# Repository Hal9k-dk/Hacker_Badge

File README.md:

# Hacker_Badge
HAL9K member PCB badge 
See more at http://wiki.hal9k.dk/projects/hacker_badge

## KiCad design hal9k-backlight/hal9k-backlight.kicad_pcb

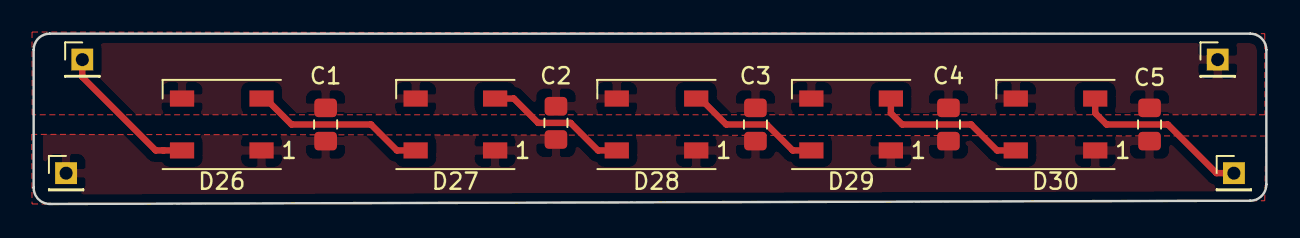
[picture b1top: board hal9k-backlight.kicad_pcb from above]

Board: 2 copper layers, 76.0 x 10.5 mm, 14 parts (0 on the bottom side), 8 nets.

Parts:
C1, C2, C3, C4, C5: C; C_0805_2012Metric_Pad1.15x1.40mm_HandSolder
D26, D27, D28, D29, D30: WS2812B; LED_WS2812B_PLCC4_5.0x5.0mm_P3.2mm
J1: +; PinHeader_1x01_P2.00mm_Vertical
J2: GND; PinHeader_1x01_P2.00mm_Vertical
J3: Din; PinHeader_1x01_P2.00mm_Vertical
J4: Dout; PinHeader_1x01_P2.00mm_Vertical

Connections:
+BATT: C1.1, C2.1, C3.1, C4.1, C5.1, D26.1, D27.1, D28.1, D29.1, D30.1, J1.1
GND: C1.2, C2.2, C3.2, C4.2, C5.2, D26.3, D27.3, D28.3, D29.3, D30.3, J2.1
unnamed: D26.2, D27.4
unnamed: D26.4, J3.1
unnamed: D27.2, D28.4
unnamed: D28.2, D29.4
unnamed: D29.2, D30.4
unnamed: D30.2, J4.1

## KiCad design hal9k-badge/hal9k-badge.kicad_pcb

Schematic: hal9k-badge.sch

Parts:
C1, C6: 10uF; C_0805_HandSoldering
C2, C5, C7, C8, C9, C10, C11, C12, C13, C14, C15, C16, C17, C18, C19, C20, C21, C22, C23, C24, C25, C26, C27, C28, C29, C30, C31, C32, C33, C34, C35, C36: 100nF; C_0805_HandSoldering
C3, C4: 1uF; C_0805_HandSoldering
C37, C38, C39, C40: 22pF; C_0603_HandSoldering
D1, D2, D3, D4, D5, D6, D7, D8, D9, D10, D11, D12, D13, D14, D15, D16, D17, D18, D19, D20, D21, D22, D23, D24, D25: WS2812B; LED_WS2812B_PLCC4_5.0x5.0mm_P3.2mm
D26: 1N5819; D_0805_2012Metric_Pad1.15x1.40mm_HandSolder
D27: L13; LED_0603_1608Metric_Pad1.05x0.95mm_HandSolder
D28: USB; LED_0603_1608Metric_Pad1.05x0.95mm_HandSolder
J1: Din; PinHeader_1x01_P2.00mm_Vertical
J2: +; PinHeader_1x01_P2.00mm_Vertical
J3, J13, J14: GND; PinHeader_1x01_P2.00mm_Vertical
J4: Dout; PinHeader_1x01_P2.00mm_Vertical
J5: USB_B_Micro; USB_Micro-B_Molex_47346-0001
J6: ISCP_ATMEGA; Pin_Header_Straight_2x03_Pitch2.54mm
J7: SHITTY_ADD_ON; Pin_Header_Straight_2x02_Pitch2.54mm
J8: Display; Pin_Header_Straight_1x04_Pitch2.54mm
J15: IO_ATMEGA; PinHeader_1x20_P2.00mm_Vertical
J16: IO_ESP; PinHeader_1x12_P2.00mm_Vertical
JP1: DTR_ESP; SolderJumper-2_P1.3mm_Bridged_Pad1.0x1.5mm
JP2: RTS_ESP; SolderJumper-2_P1.3mm_Bridged_Pad1.0x1.5mm
JP3: DTR_ATMEGA; SolderJumper-2_P1.3mm_Bridged_Pad1.0x1.5mm
JP4: SolderJumper_2_Bridged; SolderJumper-2_P1.3mm_Bridged_Pad1.0x1.5mm
JP5: SDA; SolderJumper-3_P1.3mm_Open_Pad1.0x1.5mm_NumberLabels
JP6: WS2812B; SolderJumper-3_P1.3mm_Open_Pad1.0x1.5mm_NumberLabels
JP7: SCL; SolderJumper-3_P1.3mm_Open_Pad1.0x1.5mm_NumberLabels
JP8: TX-RX; SolderJumper-2_P1.3mm_Open_Pad1.0x1.5mm
JP9: RX-TX; SolderJumper-2_P1.3mm_Open_Pad1.0x1.5mm
M1: lipo-charger
Q1, Q2: S8050; SOT-23
R1, R2, R3, R4, R5, R6, R9, R10, R13, R14: 10kOHM; R_0805_HandSoldering
R7, R8: 47OHM; R_0805_HandSoldering
R11, R12: 330OHM; R_0805_HandSoldering
S1: Reset Esp; SW_SPST_FSMSM
S2: SELECT; SW_SPDT_PCM12
S3: Reset Atmega; SW_SPST_FSMSM
S4: POWER; SW_SPDT_PCM12
U1: ESP-12F; ESP-12_SMD
U2: PMIC-LDO-XC6206P332MR-G(SOT23); SOT-23
U3: CH340G; SOIC-16_3.9x9.9mm_Pitch1.27mm
U4: ATmega328P-AU; TQFP-32_7x7mm_P0.8mm
U5: MC14053BDG; SOIC-16_3.9x9.9mm_Pitch1.27mm
Y1: 12MHz; OSC_CSTCE16M0V53-R0
Y2: 16MHz; OSC_CSTCE16M0V53-R0
Y3: 12MHz; Crystal_SMD_HC49-SD
Y4: 16MHz; Crystal_SMD_HC49-SD

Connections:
+3V3: C4.1, C6.1, C8.1, C11.1, S2.1, U2.2, U3.4, U3.16, U5.16
+5V: C3.1, D26.1 (K), R12.2, U2.3
+BATT: C1.1, C2.1, C7.1, C12.1, C13.1, C14.1, C15.1, C16.1, C17.1, C18.1, C19.1, C20.1, C21.1, C22.1, C23.1, C24.1, C25.1, C26.1, C27.1, C28.1, C29.1, C30.1, C31.1, C32.1, C33.1, C34.1, C35.1, C36.1, D1.1, D2.1, D3.1, D4.1, D5.1, D6.1, D7.1, D8.1, D9.1, D10.1, D11.1, D12.1, D13.1, D14.1, D15.1, D16.1, D17.1, D18.1, D19.1, D20.1, D21.1, D22.1, D23.1, D24.1, D25.1, J2.1, J7.2, J8.2, J15.19, J16.1, R1.1, R2.1, R3.1, R9.2, R10.2, R13.2, R14.2, S4.2, U1.8, U4.4 (VCC), U4.6 (VCC), U4.18 (AVCC)
ATMEGA_2: J15.1, U4.32 (PD2)
ATMEGA_3: J15.2, U4.1 (PD3)
ATMEGA_4: J15.3, U4.2 (PD4)
ATMEGA_5: J15.4, U4.9 (PD5)
ATMEGA_6: J15.5, JP6.1, U4.10 (PD6)
ATMEGA_7: J15.6, U4.11 (PD7)
ATMEGA_8: J15.7, U4.12 (PB0)
ATMEGA_9: J15.8, U4.13 (PB1)
ATMEGA_10: J15.9, U4.14 (PB2)
ATMEGA_11: J6.4, J15.10, U4.15 (PB3)
ATMEGA_12: J6.1, J15.11, U4.16 (PB4)
ATMEGA_13: J6.3, J15.12, R11.2, U4.17 (PB5)
ATMEGA_A0: J15.13, U4.23 (PC0)
ATMEGA_A1: J15.14, U4.24 (PC1)
ATMEGA_A2: J15.15, U4.25 (PC2)
ATMEGA_A3: J15.16, U4.26 (PC3)
ATMEGA_A4_SDA: J15.17, JP5.1, U4.27 (PC4)
ATMEGA_A5_SCL: J15.18, JP7.1, U4.28 (PC5)
ATMEGA_A6: U4.19 (ADC6)
ATMEGA_A7: U4.22 (ADC7)
ATMEGA_AREF: C9.1, U4.20 (AREF)
ATMEGA_RESET: C10.1, J6.5, R10.1, S3.2, U4.29 (~RESET~/PC6)
ATMEGA_RX: JP9.2, U4.30 (PD0), U5.12
ATMEGA_TX: JP8.2, U4.31 (PD1), U5.2
CH340_ATMEGA_DTR: JP3.1, U5.5
CH340_DTR: U3.13, U5.4
CH340_ESP_DTR: JP1.1, U5.3
CH340_RTS: JP2.1, U3.14
CH340_RX: R8.1, U5.15
CH340_TX: R7.1, U5.14
ESP_0: J16.6, Q2.3, R2.2, U1.12
ESP_2: J16.5, R3.2, U1.11
ESP_4_SDA: J16.7, JP5.3, U1.13
ESP_5_SCL: J16.8, JP7.3, U1.14
ESP_12: J16.3, U1.6
ESP_13: J16.2, U1.7
ESP_14: J16.10, U1.5
ESP_15: J16.4, R4.2, U1.10
ESP_16: J16.11, U1.4
ESP_ADC: J16.12, U1.2
ESP_CHPD: R1.2, U1.3
ESP_RESET: C5.2, Q1.3, R9.1, S1.2, U1.1
ESP_RX: JP6.3, JP8.1, U1.15, U5.13
ESP_TX: JP9.1, U1.16, U5.1
FTDI_ATMEGA_DTR: C10.2, JP3.2
FTDI_ESP_DTR: JP1.2, Q2.2, R5.1
FTDI_ESP_RTS: JP2.2, Q1.2, R6.1
GND: C1.2, C2.2, C3.2, C4.2, C5.1, C6.2, C7.2, C8.2, C9.2, C11.2, C12.2, C13.2, C14.2, C15.2, C16.2, C17.2, C18.2, C19.2, C20.2, C21.2, C22.2, C23.2, C24.2, C25.2, C26.2, C27.2, C28.2, C29.2, C30.2, C31.2, C32.2, C33.2, C34.2, C35.2, C36.2, C37.2, C38.2, C39.1, C40.1, D1.3, D2.3, D3.3, D4.3, D5.3, D6.3, D7.3, D8.3, D9.3, D10.3, D11.3, D12.3, D13.3, D14.3, D15.3, D16.3, D17.3, D18.3, D19.3, D20.3, D21.3, D22.3, D23.3, D24.3, D25.3, D27.1, D28.1, J3.1, J5.5, J5.6, J6.6, J7.1, J8.1, J13.1, J14.1, J15.20, J16.9, JP4.1, M1.2, M1.3, R4.1, S1.1, S2.3, S3.1, U1.9, U2.1, U3.1, U4.3 (GND), U4.5 (GND), U4.21 (GND), U5.7, U5.8, Y1.2, Y2.2
I2C_SCL: J7.3, J8.3, JP7.2, R13.1
I2C_SDA: J7.4, J8.4, JP5.2, R14.1
unnamed: C37.1, U3.7, Y1.1, Y3.2
unnamed: C38.1, U3.8, Y1.3, Y3.1
unnamed: C39.2, U4.7 (XTAL1/PB6), Y2.3, Y4.1
unnamed: C40.2, U4.8 (XTAL2/PB7), Y2.1, Y4.2
unnamed: D1.2, D2.4
unnamed: D2.2, D3.4
unnamed: D3.2, D4.4
unnamed: D4.2, D5.4
unnamed: D5.2, D6.4
unnamed: D6.2, D7.4
unnamed: D7.2, D8.4
unnamed: D8.2, D9.4
unnamed: D10.2, D11.4
unnamed: D9.2, D10.4
unnamed: D11.2, D12.4
unnamed: D12.2, D13.4
unnamed: D13.2, D14.4
unnamed: D14.2, D15.4
unnamed: D15.2, D16.4
unnamed: D16.2, D17.4
unnamed: D17.2, D18.4
unnamed: D18.2, D19.4
unnamed: D19.2, D20.4
unnamed: D20.2, D21.4
unnamed: D21.2, D22.4
unnamed: D22.2, D23.4
unnamed: D23.2, D24.4
unnamed: D24.2, D25.4
unnamed: D25.2, J1.1
unnamed: D27.2, R11.1
unnamed: D28.2, R12.1
unnamed: J5.2, U3.6
unnamed: J5.3, U3.5
unnamed: JP4.2, U5.6
unnamed: M1.6, S4.3
unnamed: Q1.1, R5.2
unnamed: Q2.1, R6.2
unnamed: R7.2, U3.2
unnamed: R8.2, U3.3
unnamed: S2.2, U5.9, U5.10, U5.11
VCC: D26.2 (A), J5.1, M1.1
WS2812B_Din: D1.4, JP6.2
WS2812B_Dout: J4.1

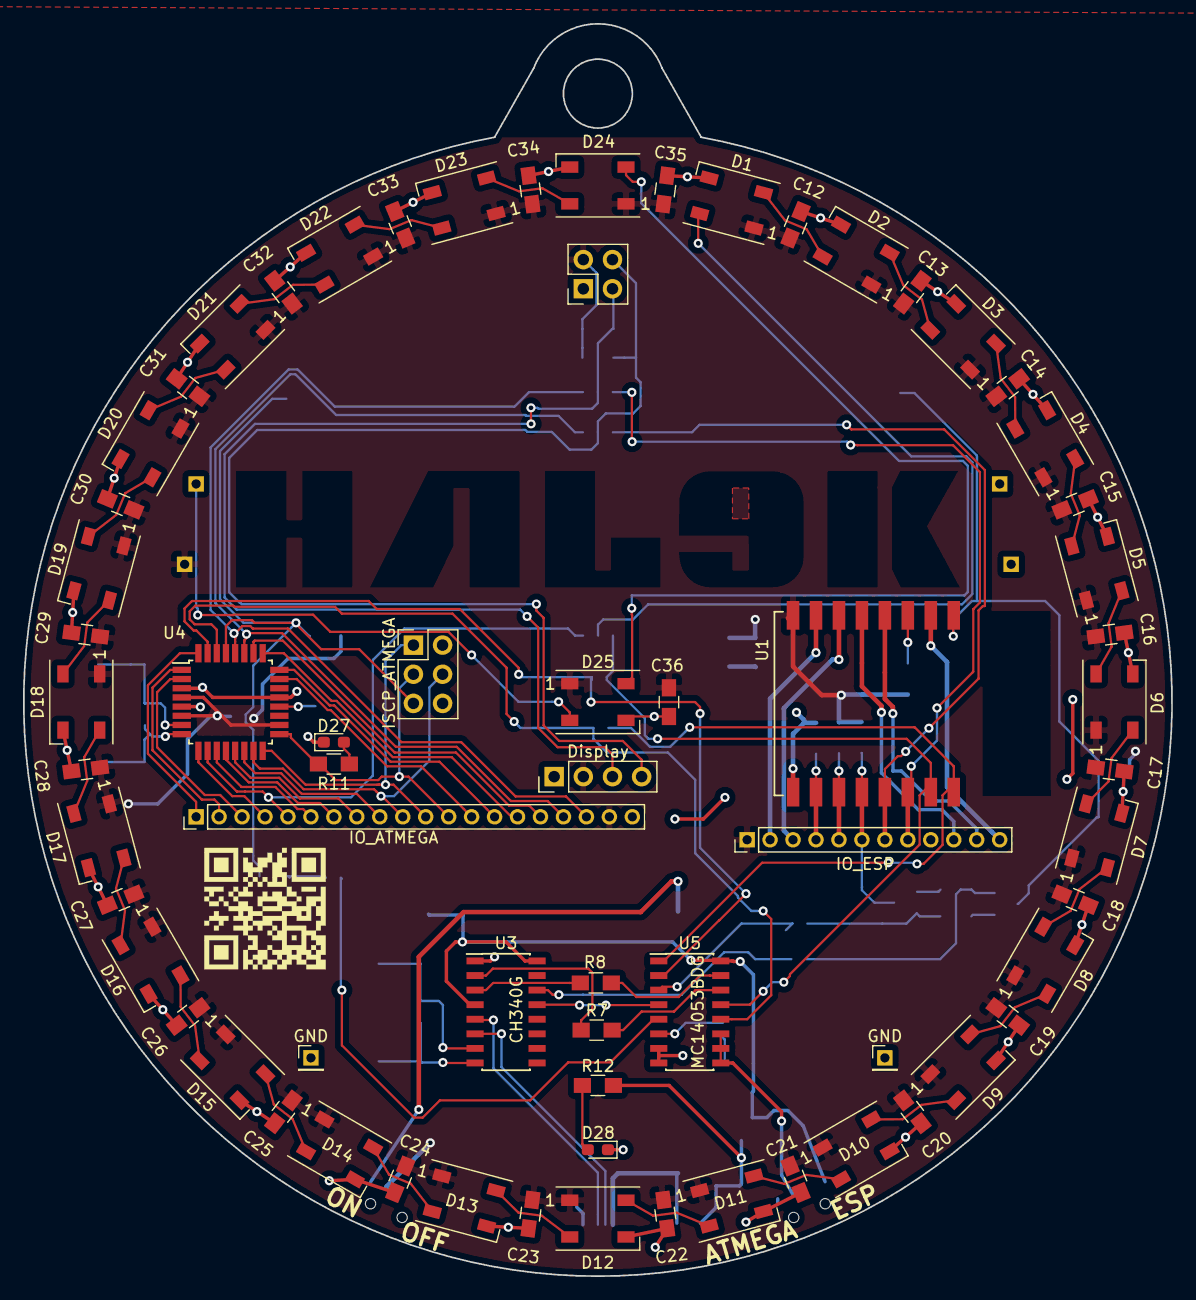
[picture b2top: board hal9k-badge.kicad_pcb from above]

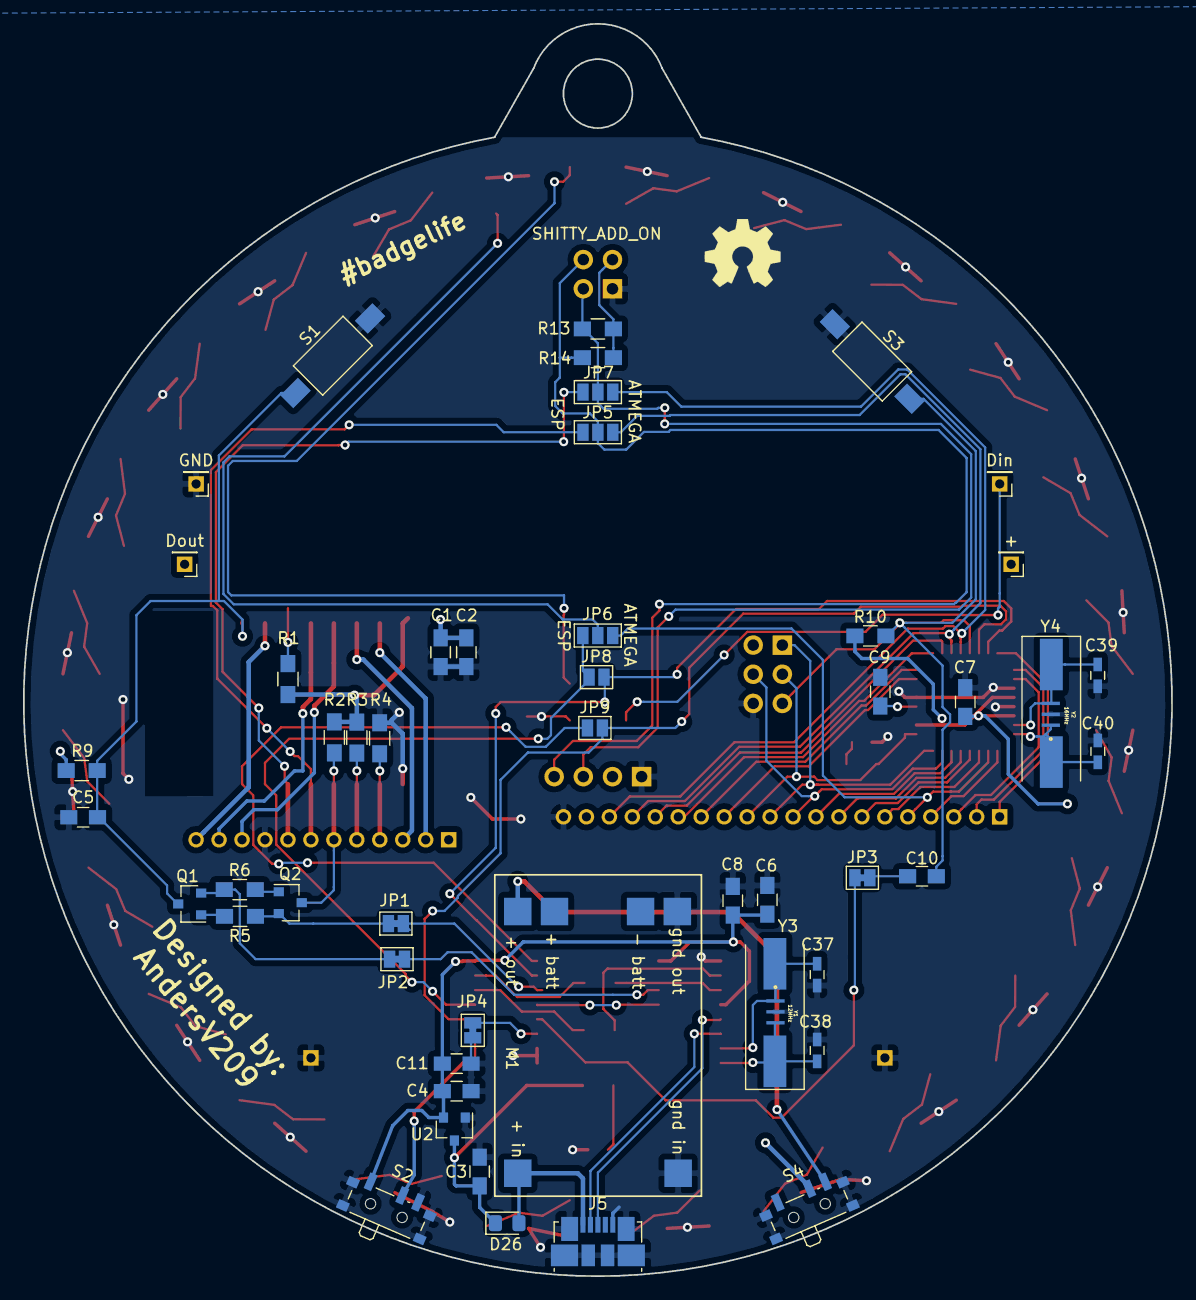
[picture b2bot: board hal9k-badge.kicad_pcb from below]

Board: 2 copper layers, 100.0 x 109.1 mm, 119 parts (52 on the bottom side), 93 nets.

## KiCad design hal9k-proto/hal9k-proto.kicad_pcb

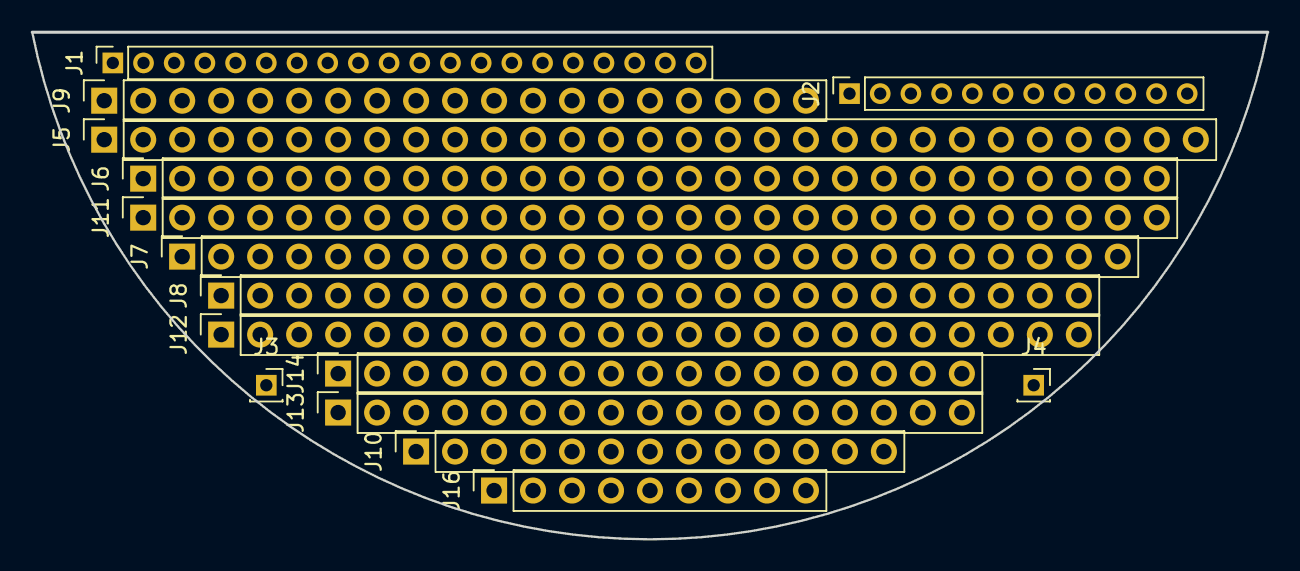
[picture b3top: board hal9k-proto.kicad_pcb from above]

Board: 2 copper layers, 80.5 x 33.0 mm, 15 parts (0 on the bottom side), 2 nets, no tracks yet.

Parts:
J1: Conn_01x20; PinSocket_1x20_P2.00mm_Vertical
J2: Conn_01x12; PinSocket_1x12_P2.00mm_Vertical
J3, J4: Conn_01x01; PinSocket_1x01_P2.00mm_Vertical
J5: Conn_01x29; PinSocket_1x29_P2.54mm_Vertical
J6, J11: Conn_01x27; PinSocket_1x27_P2.54mm_Vertical
J7: Conn_01x25; PinSocket_1x25_P2.54mm_Vertical
J8, J12: Conn_01x23; PinSocket_1x23_P2.54mm_Vertical
J9: Conn_01x19; PinSocket_1x19_P2.54mm_Vertical
J10: Conn_01x13; PinSocket_1x13_P2.54mm_Vertical
J13, J14: Conn_01x17; PinSocket_1x17_P2.54mm_Vertical
J16: Conn_01x09; PinSocket_1x09_P2.54mm_Vertical

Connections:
+BATT: J1.19, J2.1
GND: J1.20, J2.9, J3.1, J4.1

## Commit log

2018-09-11 backlight update
2018-09-11 Badge update
2018-09-30 silkscreen for backlight fix in gerber
